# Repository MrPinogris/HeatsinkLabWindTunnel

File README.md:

# HeatsinkLab Wind Tunnel

ESP32-S3 based heatsink thermal characterisation platform. A ceramic heater drives the heatsink under test to a series of set-point temperatures while a controlled fan provides forced convection through the wind tunnel. All sensor data streams to a browser-based GUI; results are saved automatically as a CSV.

---

## System Architecture

```
┌──────────────────────────────────┐
│  Firmware (C++ / ESP32-S3)       │  src/  — stable, treat as black box
│  · PID heater + fan control      │
│  · MAX6675 thermocouple (SPI)    │
│  · INA226 power monitor (I²C)    │
│  · SDP510 diff. pressure (I²C)   │
│  · EZO-HUM humidity probe (I²C)  │
│  · Serial command interface      │
└────────────┬─────────────────────┘
             │ USB Serial 115 200 baud
┌────────────▼─────────────────────┐
│  Backend  (Python / FastAPI)     │  tools/web_gui/server.py
│  · WebSocket server :8765        │
│  · Telemetry parser              │
│  · CSV logger                    │
│  · Virtual MCU simulator         │
└────────────┬─────────────────────┘
             │ WebSocket
┌────────────▼─────────────────────┐
│  Frontend (HTML / JS / CSS)      │  tools/web_gui/static/index.html
│  · Chart.js real-time graphs     │
│  · PID tuning controls           │
│  · Tester workflow (automated)   │
│  · CSV export                    │
└──────────────────────────────────┘
```

---

## Hardware

### Component Summary

| Component | Part | Interface | I²C Address |
|---|---|---|---|
| MCU | ESP32-S3 DevKit-C1 | — | — |
| Temperature sensor | MAX6675 thermocouple module | SPI | — |
| Power monitor | INA226 (A0 → VCC) | I²C | 0x41 |
| Differential pressure | Sensirion SDP510 | I²C | 0x40 |
| Humidity probe | EZO-HUM (Atlas Scientific) | I²C | 0x6F |
| Heater switch | MOSFET module (PWM gate) | GPIO 4 | — |
| Fan PWM | MOSFET / driver module | GPIO 5 | — |
| Fan power cut-off | MOSFET module (digital gate) | GPIO 10 | — |

### ESP32-S3 Pin Assignments

| GPIO | Function | Notes |
|---|---|---|
| 4 | Heater MOSFET gate | PWM 500 Hz, 8-bit (0–255) |
| 5 | Fan PWM signal | PWM 500 Hz, 8-bit |
| 10 | Fan power MOSFET gate | HIGH = powered, LOW = fully off |
| 11 | MAX6675 SO (MISO) | SPI |
| 12 | MAX6675 CS | SPI |
| 13 | MAX6675 SCK | SPI |
| 15 | I²C SDA | Shared bus: INA226, SDP510, EZO-HUM |
| 16 | I²C SCL | Shared bus |

---

## Wiring

### Power Distribution

```
12 V Lab PSU (+) ─────┬──────────────────── Heater MOSFET IN+
                      └──────────────────── Fan MOSFET IN+
12 V Lab PSU (−) ─────┬──────────────────── Heater MOSFET IN−
                      ├──────────────────── Fan MOSFET IN−
                      └──────────────────── ESP32 GND (common)
```

### Heater Power Path

```
12 V (+) → Heater MOSFET IN+
           Heater MOSFET OUT+ → Heater element (+)
           Heater element (−) → INA226 IN+
                                INA226 IN−  → Heater MOSFET OUT−
12 V (−) → Heater MOSFET IN−  (common GND)

ESP GPIO 4  → Heater MOSFET signal
ESP GND     → Heater MOSFET signal GND
```

INA226 shunt is wired in series with the heater so it measures heater current directly.

### Fan Power Path

```
12 V (+) → Fan MOSFET (power cut-off) IN+
           Fan MOSFET OUT+ → Fan (+) / PWM driver IN+
12 V (−) → Fan MOSFET IN−  (common GND)

ESP GPIO 5  → Fan PWM signal
ESP GPIO 10 → Fan power MOSFET gate  (HIGH = fan enabled, LOW = fully off)
ESP GND     → Fan MOSFET signal GND
```

### MAX6675 Thermocouple (SPI)

| MAX6675 Pin | Connects to |
|---|---|
| VCC | ESP32 3.3 V |
| GND | ESP32 GND |
| SCK | GPIO 13 |
| CS  | GPIO 12 |
| SO  | GPIO 11 |

### INA226 Power Monitor (I²C, 0x41)

| INA226 Pin | Connects to |
|---|---|
| VCC | ESP32 3.3 V |
| GND | ESP32 GND |
| SDA | GPIO 15 |
| SCL | GPIO 16 |
| A0  | 3.3 V (sets address to 0x41) |
| A1  | GND |
| IN+ | Heater element output |
| IN− | Heater MOSFET drain |
| ALE | Not connected |

### Sensirion SDP510 Differential Pressure (I²C, 0x40)

| SDP510 Pin | Connects to |
|---|---|
| VCC | ESP32 3.3 V |
| GND | ESP32 GND |
| SDA | GPIO 15 (shared I²C bus) |
| SCL | GPIO 16 (shared I²C bus) |

Sensor is mounted across the wind tunnel to measure pressure drop (Pa) between inlet and outlet.

### EZO-HUM Humidity Probe (I²C, 0x6F)

| EZO-HUM Pin | Connects to |
|---|---|
| VCC (red) | ESP32 3.3 V |
| GND (black) | ESP32 GND |
| SDA (green) | GPIO 15 (shared I²C bus) |
| SCL (white) | GPIO 16 (shared I²C bus) |
| AUTO (blue) | Not connected |

> **First-time setup:** Factory default is UART mode (blinking green LED).
> Send `I2C,111\r` at 9600 baud over UART once, then power-cycle until LED is solid blue (I²C mode).

---

## Physical Assembly

See `docs/media/` for annotated photos of the physical build. Key assembly features:

- **Wind tunnel inlet** — Fan with a hexagonal (honeycomb) grid immediately downstream to break up turbulence and produce laminar airflow through the tunnel.
- **Fan guard** — A protective shield covers the fan face to prevent contact injury during operation.
- **Heater module** — Ceramic PTC heater element topped with a copper spreader plate. The thermocouple is inserted into a precision-drilled hole in the copper plate to measure the heatsink base temperature accurately. The heatsink under test clips onto the copper plate.
- **Dev board** — All MOSFET switching modules, the INA226, and the ESP32-S3 DevKit are mounted on the dev board. The connector row (left to right) carries: humidity sensor, differential pressure sensor, and fan motor.
- **Expansion** — One additional MOSFET module on the left of the fan motor connector provides the independent power cut-off for the fan (GPIO 10), allowing the fan to be fully de-energised for natural-convection tests.

---

## Flashing the Firmware

Requires [PlatformIO](https://platformio.org/) (VS Code extension or CLI).

```bash
pio run -t upload      # Build and flash to connected ESP32-S3
pio run                # Build only (no upload)
```

> The firmware source is under `src/` and is considered stable. Do not modify it without reviewing `CLAUDE.md` first.

---

## Web GUI

### Requirements

- Windows 10/11 (Linux/macOS also supported)
- Python 3.10 or newer

### Install & Run

```bash
cd tools/web_gui
pip install -r requirements.txt
python server.py
```

Browser opens automatically at **http://localhost:8765**.

**Quickstart (Windows):** double-click `tools/web_gui/start.bat` — installs dependencies and launches the server.

### Testing without hardware

Select **VIRTUAL** from the port dropdown to use the built-in firmware simulator. No ESP32 required.

---

## Control Modes

| Mode | Behaviour |
|---|---|
| AUTO | PID loop continuously drives heater PWM toward setpoint |
| MANUAL | Fixed PWM set directly by the `MANPWM` parameter |
| SMART | PID until stable (±0.5 °C for 8 s), then locks the equilibrium PWM — used for automated Tester mode |

---

## Serial Command Reference

Commands are sent from the backend to the ESP32 over USB serial (115 200 baud):

| Command | Range | Description |
|---|---|---|
| `SET KP <f>` | float | PID proportional gain |
| `SET KI <f>` | float | PID integral gain |
| `SET KD <f>` | float | PID derivative gain |
| `SET BIAS <f>` | −255 to 255 | PID output bias |
| `SET SPBIAS <f>` | float | Setpoint offset bias |
| `SET SP <f>` | −20 to 400 °C | Temperature setpoint |
| `SET ALPHA <f>` | 0.001 to 1.0 | EMA filter coefficient |
| `SET MAXSTEP <n>` | int | Maximum PWM change per cycle |
| `SET FAN <n>` | 0 to 100 | Fan speed % |
| `SET FANINV <0/1>` | 0 or 1 | Invert fan PWM polarity |
| `SET FANPWR <ON/OFF>` | ON / OFF | Fan power MOSFET enable |
| `SET MODE <m>` | AUTO/MANUAL/SMART | Control mode |
| `SET MANPWM <f>` | 0 to 255 | Manual PWM value |
| `SET RUN <ON/OFF>` | ON / OFF | Enable / disable heater |
| `GET` | — | Print current configuration |

All parameters are bounds-checked in firmware before acceptance.

---

## Telemetry Output

The firmware emits one telemetry line per control cycle over serial. Example fields:

```
Rawtemp <°C>  Temp: <°C>  Smooth: <°C>  PWM: <0-255>
P: <f>  I: <f>  D: <f>  OUT: <f>  BIAS: <f>  SPBIAS: <f>
SP: <°C>  EFFSP: <°C>  FAN: <%>  FANPWM: <raw>
MODE: <AUTO|MANUAL|SMART>  STATE: <PID|HOLD|MANUAL>
MANPWM: <f>  HOLDPWM: <f>  ENTPROG: <%>  EXTPROG: <%>  EABS: <°C>
RUN: <ON|OFF>  FANINV: <0|1>
V: <V>  I: <A>  W: <W>  EQPWM: <0-255>  FANPWR: <ON|OFF>
HUMIDITY: <%>  HUM_TEMP: <°C>
DELTA_P1: <Pa>  DELTA_P1F: <Pa>  DELTA_P2: <Pa>  DELTA_P2F: <Pa>
```

---

## CSV Schema

Raw telemetry is logged to `logs/serial_<timestamp>.csv`. Schema version 4.

```
timestamp_iso, elapsed_s, raw_temp_c, temp_filtered_c, temp_smooth_c,
pwm, p_term, i_term, d_term, pid_out, pid_bias, setpoint_bias_c,
setpoint_c, effective_setpoint_c, fan_speed_pct, fan_pwm_raw, fan_power,
mode, state, manual_pwm_cmd, hold_pwm, enter_progress_pct,
exit_progress_pct, abs_error_c, run_state, fan_inverted,
vin, iin, pin, eq_pwm,
delta_p1, delta_p1f, delta_p2, delta_p2f,
humidity_pct, hum_temp_c,
event
```

Results CSV (one row per test temperature):

```
timestamp, run_id, heatsink_id, sp_temp, temp, amb_temp,
pwm_heater, fan_cmd, fan_pwm, airspeed, delta_p1, delta_p2,
humidity_pct, vin, iin, pin, mode, state, event
```

---

## Future Sensors

The system is designed for zero-disruption sensor additions. The `ExtSensorRegistry` in firmware provides named slots; the backend `TELEM_RE` regex accepts new named fields without breaking the existing parser.

| Sensor | CSV Fields | Status |
|---|---|---|
| Airspeed / anemometer | `airspeed` (m/s) | Planned — hardware not yet wired |
| Differential pressure (second port) | `delta_p2`, `delta_p2f` (Pa) | Parser ready; physical port mapped to 0 |
| Ambient humidity (additional) | `humidity_pct` | EZO-HUM implemented; Sensirion variant planned |

See `CLAUDE.md` for the 4-step pattern to add any new sensor without breaking existing data flows.

---

## Repository Structure

```
HeatsinkLabWindTunnel/
├── src/                        Firmware (C++ / PlatformIO)
│   ├── main.cpp                Setup, loop, control FSM
│   ├── PIDController.cpp/h     PID controller
│   ├── SensorManager.cpp/h     Sensor reads, EMA, glitch reject
│   ├── SerialProtocol.cpp/h    Serial command handler + telemetry emitter
│   ├── ExtSensorRegistry.cpp/h Named slot registry for future sensors
│   └── SystemState.h           Shared state struct + ControlMode enum
├── tools/web_gui/
│   ├── server.py               FastAPI backend + WebSocket + CSV logger
│   ├── static/index.html       Single-file browser GUI
│   ├── requirements.txt        Python dependencies
│   ├── start.bat               Windows one-click launcher
│   └── MANUAL.md               User-facing operating manual
├── docs/
│   ├── hardware.md             Detailed hardware reference (this thesis)
│   ├── Connections.txt         Raw wiring connection list
│   ├── media/                  Annotated build photographs
│   └── Todo.md                 Development task list
├── notes/
│   └── Ideas.md                Feature backlog with prioritisation scores
├── platformio.ini              PlatformIO build configuration
└── CLAUDE.md                   AI agent working instructions
```

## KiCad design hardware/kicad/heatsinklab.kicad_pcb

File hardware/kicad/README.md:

# HeatsinkLab Carrier Board — KiCad Project

Open `heatsinklab.kicad_pro` in KiCad 8.

## Files
- `heatsinklab.kicad_pro` — project settings and net classes
- `heatsinklab.kicad_sch` — full schematic
- `heatsinklab.kicad_pcb` — PCB layout (160 mm × 120 mm)

## After opening in KiCad

1. **Schematic**: Run *Tools → Update PCB from Schematic* to sync any edits.
2. **PCB**: Run the DRC, then route the remaining ratsnest connections.  
   Use the **Zone** tool (copper pour) for the GND plane.
3. **Footprints**: All standard KiCad 8 library footprints — no custom libs needed.

## Net classes (already configured)

| Class | Track width | Applies to |
|-------|-------------|------------|
| Default | 0.25 mm | GPIO signals, I2C, SPI |
| Power | 2.0 mm | +12V, GND, HEATER*, FAN_PWR* |

## Heater path warning

The +12V → Q1 → INA226 → J2 trace carries up to ~3–5 A.  
Route it as a **wide copper pour zone** (≥5 mm) or solder wire on top of the copper tape.

## Board dimensions

160 mm × 120 mm, 4× M3 mounting holes at corners.

## Component placement (as placed in PCB file)

| Ref | Component | XY (mm) |
|-----|-----------|---------|
| J1  | PWR_IN 2p | 12, 15 |
| J2  | HEATER_OUT 2p | 12, 35 |
| J4  | FAN_OUT 2p | 12, 50 |
| J5  | FAN_PWM 2p | 12, 65 |
| J6  | THERMO 5p | 148, 15 |
| J7  | INA226 4p | 148, 40 |
| J8  | SDP510 4p | 148, 60 |
| J9  | EZO-HUM 4p | 148, 80 |
| J10 | EXT1 4p | 148, 100 |
| Q1  | IRLZ44N Heater | 50, 30 |
| Q2  | IRLZ44N Fan | 50, 55 |
| R1  | 4.7k SDA pull-up | 120, 38 |
| R2  | 4.7k SCL pull-up | 120, 48 |
| R3  | 10k Q1 gate pull-down | 35, 30 |
| R4  | 10k Q2 gate pull-down | 35, 55 |
| U1  | ESP32-S3 dev board header | 80, 60 |

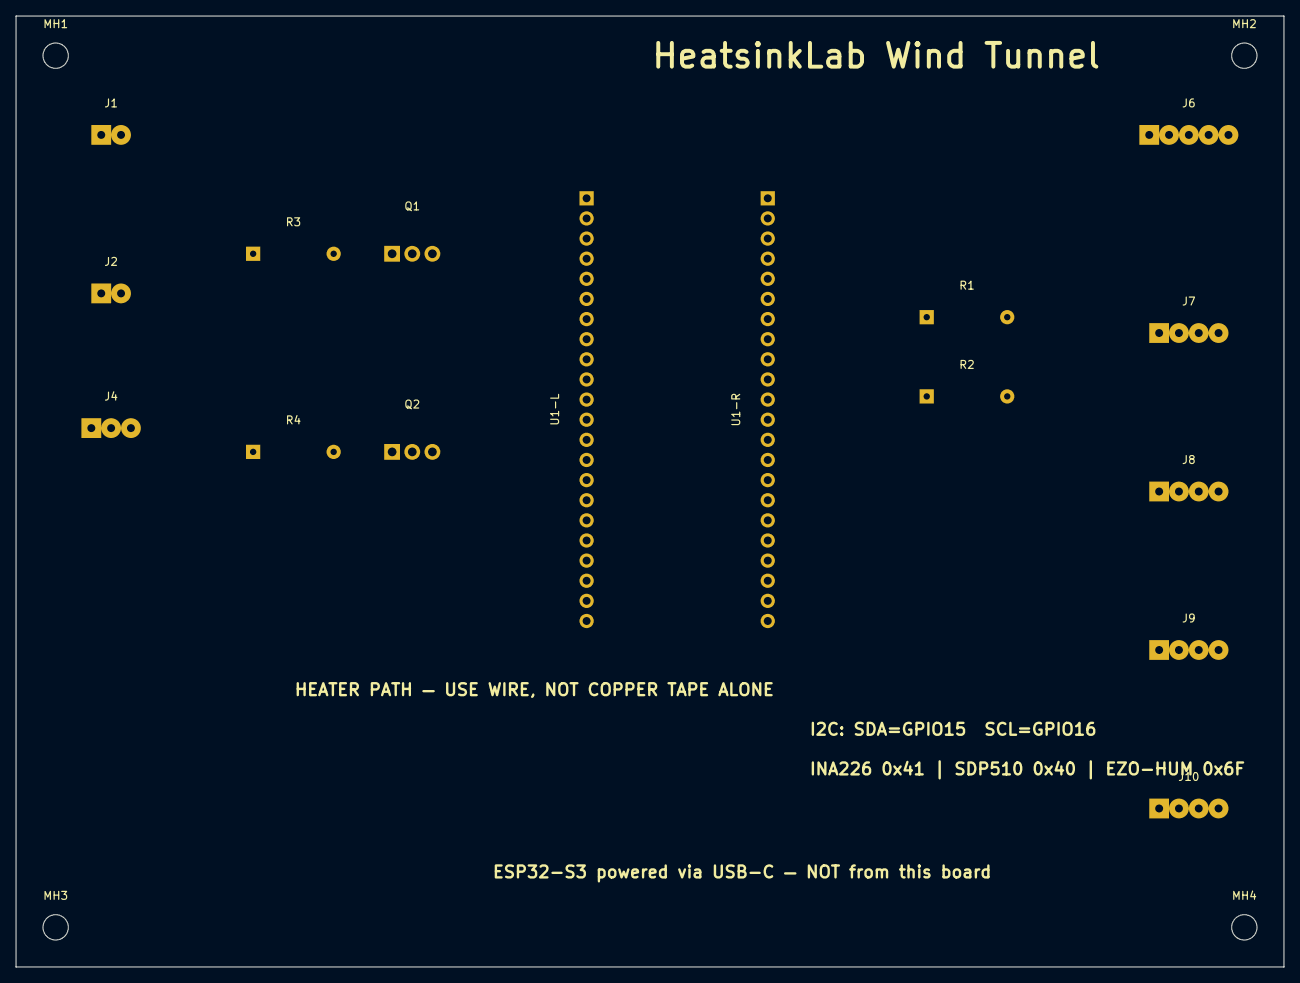
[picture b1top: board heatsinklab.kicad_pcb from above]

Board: 2 copper layers, 160.0 x 120.0 mm, 20 parts (0 on the bottom side), 11 nets, no tracks yet.

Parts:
J1: PWR_IN 12V; JST_XH_B2B-XH-A_1x02_P2.50mm_Vertical
J2: HEATER_OUT; JST_XH_B2B-XH-A_1x02_P2.50mm_Vertical
J4: FAN 12V/GND/PWM; JST_XH_B3B-XH-A_1x03_P2.50mm_Vertical
J6: THERMO MAX6675; JST_XH_B5B-XH-A_1x05_P2.50mm_Vertical
J7: INA226 0x41; JST_XH_B4B-XH-A_1x04_P2.50mm_Vertical
J8: SDP510 0x40; JST_XH_B4B-XH-A_1x04_P2.50mm_Vertical
J9: EZO-HUM 0x6F; JST_XH_B4B-XH-A_1x04_P2.50mm_Vertical
J10: EXT1 Future; JST_XH_B4B-XH-A_1x04_P2.50mm_Vertical
MH1, MH2, MH3, MH4: MountingHole; MountingHole_3.2mm_M3
Q1: IRLZ44N Heater; TO-220-3_Vertical
Q2: IRLZ44N Fan; TO-220-3_Vertical
R1: 4.7k SDA; R_Axial_DIN0207_L6.3mm_D2.5mm_P10.16mm_Horizontal
R2: 4.7k SCL; R_Axial_DIN0207_L6.3mm_D2.5mm_P10.16mm_Horizontal
R3, R4: 10k Gate GND; R_Axial_DIN0207_L6.3mm_D2.5mm_P10.16mm_Horizontal
U1-L: ESP32-S3-DevKitC-1 Left; PinHeader_1x22_P2.54mm_Vertical
U1-R: ESP32-S3-DevKitC-1 Right; PinHeader_1x22_P2.54mm_Vertical

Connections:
+3.3V: J6.1, J7.1, J8.1, J9.1, J10.1, R1.1, R2.1, U1-L.1, U1-L.2
FAN_OUT_P: J4.1, Q2.2
GND: J1.2, J2.2, J4.2, J6.2, J7.2, J8.2, J9.2, J10.2, Q1.3, Q2.3, R3.2, R4.2, U1-L.22, U1-R.1, U1-R.21, U1-R.22
GPIO4_HEAT: Q1.1, R3.1, U1-L.4
GPIO5_FPWM: J4.3, U1-L.5
GPIO10_FEN: Q2.1, R4.1, U1-L.16
I2C_SCL: J7.4, J8.4, J9.4, R2.2, U1-L.9
I2C_SDA: J7.3, J8.3, J9.3, R1.2, U1-L.8
SPI_CS: J6.4, U1-L.18
SPI_MISO: J6.3, U1-L.17
SPI_SCK: J6.5, U1-L.19

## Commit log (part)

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2026-02-25 Upload1
2026-02-25 updated gitignore
2026-02-25 made it possible to edit the PID controls and also it in a GUI
2026-03-02 added a Fan and made the speed variable via the GUI
2026-03-03 feat(control): add SMART PWM hold mode with visible handover/fallback progress
    - Add control modes AUTO/MANUAL/SMART with persisted mode and manual PWM
    - Implement SMART supervisor: PID -> learned constant HOLD PWM -> auto fallback to PID on drift
    - Add fractional PWM dithering for non-integer hold/manual PWM targets
    - Improve SMART stability logic with noise-tolerant decay counter and tuned thresholds
    - Make SMART thresholds thermocouple-accuracy aware (0.25 C based bands)
    - Emit telemetry for MODE/STATE/MANPWM/HOLDPWM and ENTPROG/EXTPROG/EABS
2026-03-03 feat: add SMART PID lab workflow improvements, integrated GUI CSV logging, runtime RUN/FANINV controls, and enhanced plotting/slider UX
2026-03-03 docs(planning): add prioritized roadmap framework and upgrade-proof CSV schema v2
    - Add scoring model to notes/Ideas.md:
    - Importance, Necessity, Dependency, Effort
    - formula: Score = 2*Importance + 2*Necessity + 2*Dependency - Effort
    - Add reusable backlog item template with acceptance criteria fields
    - Add phased roadmap (P0/P1/P2) aligned to heatsink testing, power sensor, and airflow sensors
    - Update tools/README.md with CSV Schema v2 guidance:
2026-03-03 added feature of using installes and having an fully function program in the end
2026-03-10 added library for INA226
2026-04-07 added todo
2026-05-05 fix: add pressure columns to CSV column selector dialog
    Added a 'Pressure' group to CSV_COLUMN_GROUPS containing
    delta_p1_pa, delta_p1f_pa, delta_p2_pa, delta_p2f_pa, and
    registered their Excel Power Query types as 'type number'
    in CSV_EXCEL_TYPES so they appear in the Select CSV Columns modal.
    https://claude.ai/code/session_0159LnqJ3cA82ABviT8ZqiDa
2026-05-08 Fix PC performance degradation after ~500s of serial connection (issue #12)
    Three root causes addressed:
    1. broadcast() held ws_lock across sequential await ws.send_text() calls.
    A slow or backgrounded browser tab stalled every subsequent broadcast,
    causing run_coroutine_threadsafe futures to pile up in the asyncio queue.
    Fixed: snapshot websockets list under lock (no IO), then send to all
    clients concurrently via asyncio.gather with a 3-second per-client
2026-05-11 Replace SDP2000-L analog with SDP610 I2C; fix INA226 address
    Hardware change: SDP610 wired to existing I2C bus (SDA=GPIO15, SCL=GPIO16).
    INA226 A0 already wired to VCC → address moved from 0x40 to 0x41.
    SensorManager.cpp:
    - INA226 address 0x40 → 0x41 (A0 to VCC)
    - Remove all analog ADC pressure constants and code (P_R1, P_R2, divider
    gain, ADC oversampling, voltage conversion formula)
2026-05-11 Revert "Fix ESP32 I2C timeout for SDP610 clock stretching (Error 263)"
    This reverts commit 287fe3fb4d9a1bebe5db7af964662d7503895f24.
2026-05-11 Reapply "Fix ESP32 I2C timeout for SDP610 clock stretching (Error 263)"
    This reverts commit 36597fffb78a570bcea2f1073f70848b2da00ccb.
2026-05-11 Add SDP510 startup diagnostic and fix sensor name in comments
    Prints "SDP510 OK – first reading: X.XX Pa" on boot so the serial
    monitor confirms the sensor is wired and responding before the main
    loop starts. Seeds the EMA with the first real reading instead of 0.
    Corrects SDP610→SDP510 in comments (protocol is identical, 3.3V supply).
    https://claude.ai/code/session_01G3oTXKVrqRuThGQecP4rHF
2026-05-13 fix: handshake timeout never fires when ESP sends no data
    The reader loop's `if not line: continue` guard caused the handshake
    deadline check to be skipped entirely on empty reads (0.2s serial
    timeout). On PCs where the USB-serial driver pulses DTR on port-open,
    the ESP32 resets and takes a few seconds to boot — during which it
    sends nothing. The GUI would hang at "Connecting..." indefinitely with
    no error.
2026-05-15 Add student-facing test page with 2D wind×temperature matrix
    - New student.html served at GET / — clean zero-friction UI for students:
    Step 1 Connect (port wizard + handshake indicator), Step 2 Heatsink ID,
    Step 3 test config (temperature range start/stop/step + wind speed checkboxes),
    big START TEST button, live progress with Chart.js + series selector,
    results table grouped by wind speed, auto-download on completion.
    - 2D test matrix: outer loop iterates selected fan %, inner loop steps
2026-05-25 chore: repo cleanup — remove schematic folder, fix gitignore, fix publish.bat
    - Remove KiCad schematic folder (no longer needed)
    - Remove tracked runtime/cache files: pid_gui_state.json, __pycache__/*.pyc, .claude/worktrees/
    - Fix .gitignore: correct pid_gui_state.json path, add __pycache__/, *.pyc, .claude/
    - Fix publish.bat: add missing src/ firmware files (SensorManager, SerialProtocol,
    ExtSensorRegistry, SystemState), student.html, and static/media/ images
    https://claude.ai/code/session_01S75npJi7EvrXo5LYNiYW5e
2026-05-25 settings
2026-05-26 Add fan power (MOSFET) support to student.html test runner
    Adds a "Fan OFF" chip to the Wind Speeds selector. When selected the
    test sends SET FANPWR OFF (instead of SET FAN X%) for that group,
    giving true zero airflow via the GPIO 10 MOSFET gate.
    - fanLabel() helper formats -1 sentinel as "Fan OFF" everywhere
    - startWindGroup() sends FANPWR OFF for fan<0, FANPWR ON + FAN X% otherwise
    - addGroupHeader/addResultRow/downloadResultsCsv all show "OFF" for fan<0
2026-05-26 Auto-fill ambient temp from humidity sensor in student.html
    When the HUM_TEMP telemetry field is present, the Ambient temp input
    is automatically updated from the sensor reading instead of requiring
    manual entry. A "(from sensor)" label in green appears next to the
    field; it shows "(manual)" when no sensor data is received.
    The field remains editable as a fallback when the sensor is not
    connected.
2026-05-26 Fix SMART HOLD not exiting on SP/fan change; reorder test to per-temp all fans; fix humidity CSV export
    - student.html: reorder test loop — outer=temperature, inner=fan speeds.
    Each temperature is heated to once; all fan speeds are swept before moving
    to the next setpoint, eliminating slow cool-down cycles between fan groups.
    - student.html: fix SMART HOLD stuck bug — after every setpoint or fan-speed
    change send SET MODE AUTO then SET MODE SMART to force the firmware out of
    HOLD regardless of the EXITCNT value stored in NVS.
2026-05-26 docs: complete documentation overhaul for thesis submission
    - README.md: rewrite with corrected hardware table (INA226 addr 0x41,
    SDP510 at 0x40, EZO-HUM at 0x6F), full pin assignment table, all
    wiring sections (heater/fan power paths, each sensor), system
    architecture diagram, serial command reference, telemetry field list,
    CSV schema, and repo structure
    - docs/hardware.md: new detailed hardware reference — BOM, ESP32 pin
2026-05-27 Fix GUI not loading on lab PCs without internet access
    Bundle Chart.js 4.4.3 locally instead of loading from cdn.jsdelivr.net.
    The CDN script tag in <head> blocks all JavaScript execution when the
    network is restricted (firewall, air-gapped labs), so neither WebSocket
    nor the port list ever initialised.
    Also pin requirements.txt to fastapi<0.136 to avoid pulling in
    starlette 1.0.0, which introduced breaking WebSocket changes on newer
2026-05-27 Fix start.bat syntax error on Spanish/non-English Windows
    LF line endings caused CMD's multiline if(...) parser to fail with
    "is was not expected" on Spanish-locale Windows. Rewrote using goto
    which is robust across all locales and line ending styles.
    Added .gitattributes to enforce CRLF for .bat/.cmd files on checkout.
    https://claude.ai/code/session_01H6cVJ816nMDHSBSLw7xmse
2026-05-27 Fix telemetry silently dropped on Python 3.14 due to wrong event loop
    asyncio.get_event_loop() does not reliably return the running loop in
    Python 3.14 when called from inside a coroutine — it can return a
    different or closed loop. state.loop was set to this bad reference at
    startup, so broadcast_sync() saw a closed loop and silently discarded
    every telemetry message without error.
    Result: the GUI showed "Connected" (handshake uses a different path)
2026-05-28 Fix GUI on air-gapped Windows PCs (Python 3.14 compatible)
    - Bundle Chart.js locally so the GUI works without internet access
    - Bundle all Python wheels for offline pip install (Python 3.12/3.13/3.14)
    - Fix start.bat syntax error on non-English Windows (goto instead of if-blocks)
    - Fix asyncio.Lock() crashing WebSocket handler silently on Python 3.14
    - Fix ClearCommError treated as fatal on incompatible USB-serial adapters
    - Fix asyncio.get_event_loop() → get_running_loop() for Python 3.14
2026-05-28 Add thermocouple cable connection instructions to Step 3
    Explains how to connect the probe cable to the MAX6675 terminal block
    on the PCB, including polarity and what to do if wired backwards.
    No photo available for this sub-step.
    https://claude.ai/code/session_016tkTU2Zf5CD2aLfbdubEH7
2026-05-30 Add KiCad 8 carrier board project (schematic + PCB layout)
    Includes .kicad_pro, .kicad_sch, and .kicad_pcb for the 160x120mm
    3D-printable ESP32-S3 carrier board with JST-XH connectors for all
    sensors, IRLZ44N MOSFETs for heater/fan, INA226, I2C pull-ups, and
    MOSFET gate pull-downs.
    https://claude.ai/code/session_01WnNzHJgAA7wxew4mtPpYTu
2026-05-30 Rewrite KiCad schematic with correct KiCad 9 s-expression syntax
    Fix net_label->label, remove invalid property inside labels, fix
    fields_autoplaced, use proper UUIDs, correct all symbol definitions.
    https://claude.ai/code/session_01WnNzHJgAA7wxew4mtPpYTu
2026-05-30 Merge FAN_OUT + FAN_PWM into single 3-pin JST-XH connector J4
    J4 now carries: pin1=12V(via Q2), pin2=GND, pin3=GPIO5_PWM.
    Removes separate J5 2-pin connector. Adds Conn_01x03 lib symbol.
    Updates PCB footprint to JST_XH_B3B-XH-A and wiring schematic doc.
    https://claude.ai/code/session_01WnNzHJgAA7wxew4mtPpYTu
2026-06-02 Revise thesis: embed real photos, remove most fills, illustrative result table
2026-06-03 Cap setpoint at 200°C via SP_MAX_C constant; update thesis
2026-06-03 Fill author, institution, supervisor; write acknowledgements
2026-06-03 Replace em/en dashes and Unicode minus with ASCII hyphens
2026-06-03 Make example result table physically realistic (finned heatsink wins)
2026-06-04 Reduce PDF margins to 2cm for tighter layout
    https://claude.ai/code/session_013nR6JyY1bGJcehLR8M8mT6
2026-06-05 Add .gitignore for LaTeX build artifacts in docs/thesis
    https://claude.ai/code/session_013nR6JyY1bGJcehLR8M8mT6
2026-06-05 Trim slide text to keyword bullets
    Slides are now lean visual aids; full talking points remain in
    presentation-notes.pdf. Speaker \note{} blocks unchanged.
    https://claude.ai/code/session_013nR6JyY1bGJcehLR8M8mT6
2026-06-09 Move start.bat and start_online.bat to repo root
    Both bat files now live at the top level so students can extract
    the zip to a short path and double-click without navigating into
    tools/web_gui. Each bat uses %~dp0 to cd into tools\web_gui before
    installing dependencies and starting the server.
    https://claude.ai/code/session_01TNYGbNJqf2fu1xgxGVZZdk
2026-06-09 Show ΔP1/ΔP2 filtered series by default in tester mode
    Add delta_p1f and delta_p2f to the tester mode default visible
    series list so pressure difference appears on the tester graph
    automatically when sensor data is available. The y3 axis uses
    display:'auto' so it stays hidden when no pressure data arrives.
    https://claude.ai/code/session_01MDGr5oMq6yGA8q2FrHRHCh
